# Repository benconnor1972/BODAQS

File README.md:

<table>
  <tr>
    <td width="50%">
      
    </td>

   <td width="50%">
      
    </td>
  </tr>
  <tr>
    <td width="50%">
      
    </td>
    <td width="50%">
      
    </td>
  </tr>
</table>

Current releases [here](https://github.com/benconnor1972/BODAQS/blob/main/RELEASES.md)

# Bicycle Open Data Acquisition System

BODAQS (Bicycle open data acquisition system) is an open-source, build-it-yourself data collection
and analysis system for mountain bikes, designed to be accessible to anyone with some DIY skills and a curiosity about what their bike is actually doing.

Data acquisition is ubiquitous in motorsport, and it's making its way into mountain-bike racing too. But for the engineering-minded (or budget-constrained), the choice is often between costly professional systems or consumer tools that keep the underlying data hidden.

BODAQS aims to offer an alternative: hardware that can be built with basic soldering skills using widely available parts; software with deep functionality and a structure designed for long-term expansion; and analysis built on powerful, free tools — alongside mounting and mechanical designs that can be 3D printed at home or produced at low cost. 

The project provides **open designs** for the hardware, software, analysis tools, and mechanical parts needed to collect and analyze mountain-bike data. It follows a build-it-yourself ethos, emphasising simplicity and low cost **without compromising functionality**.

## The problem with mountain bike (suspension) tuning

For most riders, suspension setup is a vibe-based, iterative guessing game: adjust a click, do a
run, wonder if that made things better or just 'different', repeat to exhaustion.

At the sharp end of gravity racing, teams with the budget chase these problems using data - but at a high cost. A few consumer products - notably Shockwiz, now owned by SRAM - have bridged the gap with a product that can provide meaningful suspension insight for most riders and be set up in under twenty minutes. But ShockWiz is a closed system: the algorithm is proprietary, the data never leaves the device, and if you run a coil shock, you're out of luck.

For the rider who wants to go deeper, wants to do more with the data, or whose coil setup isn't
supported,the choice has been: trust a black box, go all in on professional equipment, or go
without.

## The device

The BODAQS logger is a compact, hackable, open-source data logger you build yourself from widely available
components using basic soldering skills and a 3D printer. It records inputs from suspension and other sensors, at up to 1000Hz, and stores the data as standard CSV files readable by almost anything. The device can connect to wifi to allow settings to be edited or log files downloaded using any device with a web browser.

A small OLED screen and keypad make it simple to use, and an optional
handlebar-mounted button lets you tag moments of interest mid-ride — a heavy landing, a sketchy
section — so they're easy to find later.

The full design is open: PCB schematics and layouts, firmware, case, sensor mounts and more are all available to build, hack, and improve. There's a full bill of materials, build guide and advice on where to purchase the parts required.

## The software

Recording data is an engineering problem. Deciding what it means is the harder part, and the part that actually matters for tuning.

The BODAQS software comprises two main components:

- the **Import Manager** imports data from one or more loggers via file copy or WiFi, applies bike geometry information, does pre-processing calculations, matches GPS data from external devices and manages setup notes. The processed files live in your personal run library.
- the **BODAQS Workbench** gives you the visualization tools to dig deep into what your bike is doing.
The whole package can be installed on your computer and run with or without an internet connection.

## Who it's for

BODAQS is designed to scale with the user — in both the build, and the analysis.

If you're new to data acquisition, the hardware guide walks you through assembling the
logger, and you'll have something real to look at after your first ride with a couple of sensors - or even just one. 

If you're a top-end rider, mechanic or suspension shop with your own battle-tested ideas on how a bike should be set up, you'll have something you can use to test out and validate your own ideas and work, race faster, or to add value to your customers. 

If you're a tinkerer, engineer, developer, data scientist or uncategorised nerd, you can contribute to the project. Code, designs, ideas, feedback - it's all welcome.

## Enough of the pitch - where's this thing actually at?

**TL;DR:** we've got a pretty usable first-generation system that runs from end to end: From sourcing and building your logger to analyzing your runs. There's still lots to do, but we think it can add value for most people in its current state.

- The hardware works well within the limits of what we have tested and we think the user experience is pretty good. 
- The system supports analog potentiometers for suspension displacement, AS5600 (12-bit) and AS5048B (14-bit) rotary encoders for measuring linkage rotation, and GPS (either dedicated receiver or integrating data from Garmin devices).
- We have our own end-to-end software solution that you can download and test out, as well as a [hosted demo](https://demo.bodaqs.net/). We're also compatible with [data.syn.bike](https://data.syn.bike) if you prefer to see your data presented that away.
- We have [sourcing](https://bodaqs.net/logger-build-guide/bodaqs-a8/sourcing-hardware/), [building](https://bodaqs.net/logger-build-guide/bodaqs-a8/building-the-logger/), and [user](https://bodaqs.net/user-guide/) guides.
- We have published packages for the [hardware](https://github.com/benconnor1972/BODAQS/tree/main/hardware/releases) and the [3d printed parts](https://github.com/benconnor1972/BODAQS/tree/main/mechanical/Case/a8_v1_0)
- We have a set of Jupyter Lab [analysis notebooks](https://github.com/benconnor1972/BODAQS/releases) for exploratory data analysis. The back end code is organised in Python modules and there is a documented [API](https://github.com/benconnor1972/BODAQS/blob/main/docs/analysis/contracts/BODAQS_Public_API_Contract_v0.md). 

What we're working on:
- Further development of the software. There is lots we want to do!
- Extending the range of supported sensors. We've gone heavy (overkill?) on our software design to make integration of additional sensor types simple, so now is the time to cash in. Our next priorities are wheel speed sensors and inertia-motion units.
- Collecting build feedback from our beta testers. We're looking for people who want to help with this!
- Getting the system under some faster riders - in the end, we want to do *data analysis*, not just build hardware and software.

## Ethos and inspiration

This project exists for many reasons but three specific precursors stand out:
 - ShockWiz: Nigel Wade's ground-breaking product, now owned by SRAM, is in a category of one: mountain bike suspension analysis products that can be set up by an average user in under 20 minutes and provide useful feedback to the vast majority of riders. I was a happy ShockWiz user for many years and probably still would be if I hadn't discovered coil suspension. An elegant product that extracts maximum insight from minimum hardware, with a simplicity that hides some very clever engineering.
 - Sufni: The first open-source mountain bike data acquisition project to cross my path. For a variety of reasons I decided to take a different path rather than build one, but it provided the seed of the idea and the use of Lego for sensor mounting deserves a credit of its own.
 - RepRap: The movement that gave birth to cheap and ubiquitous 3D printing wasn't driven by market analysis by some big corporation, but by people who wanted a thing they couldn't buy (at a reasonable price). The community development and sharing ethos persists to this day and the products available are massively better and cheaper than what was available just a few years ago.

## Project maintenance

BODAQS is maintained by [Ben Connor](https://github.com/benconnor1972).

Contact: benconnor1972@gmail.com

Official release and code-signing responsibilities are described in the
[Code Signing Policy](CODE_SIGNING_POLICY.md).

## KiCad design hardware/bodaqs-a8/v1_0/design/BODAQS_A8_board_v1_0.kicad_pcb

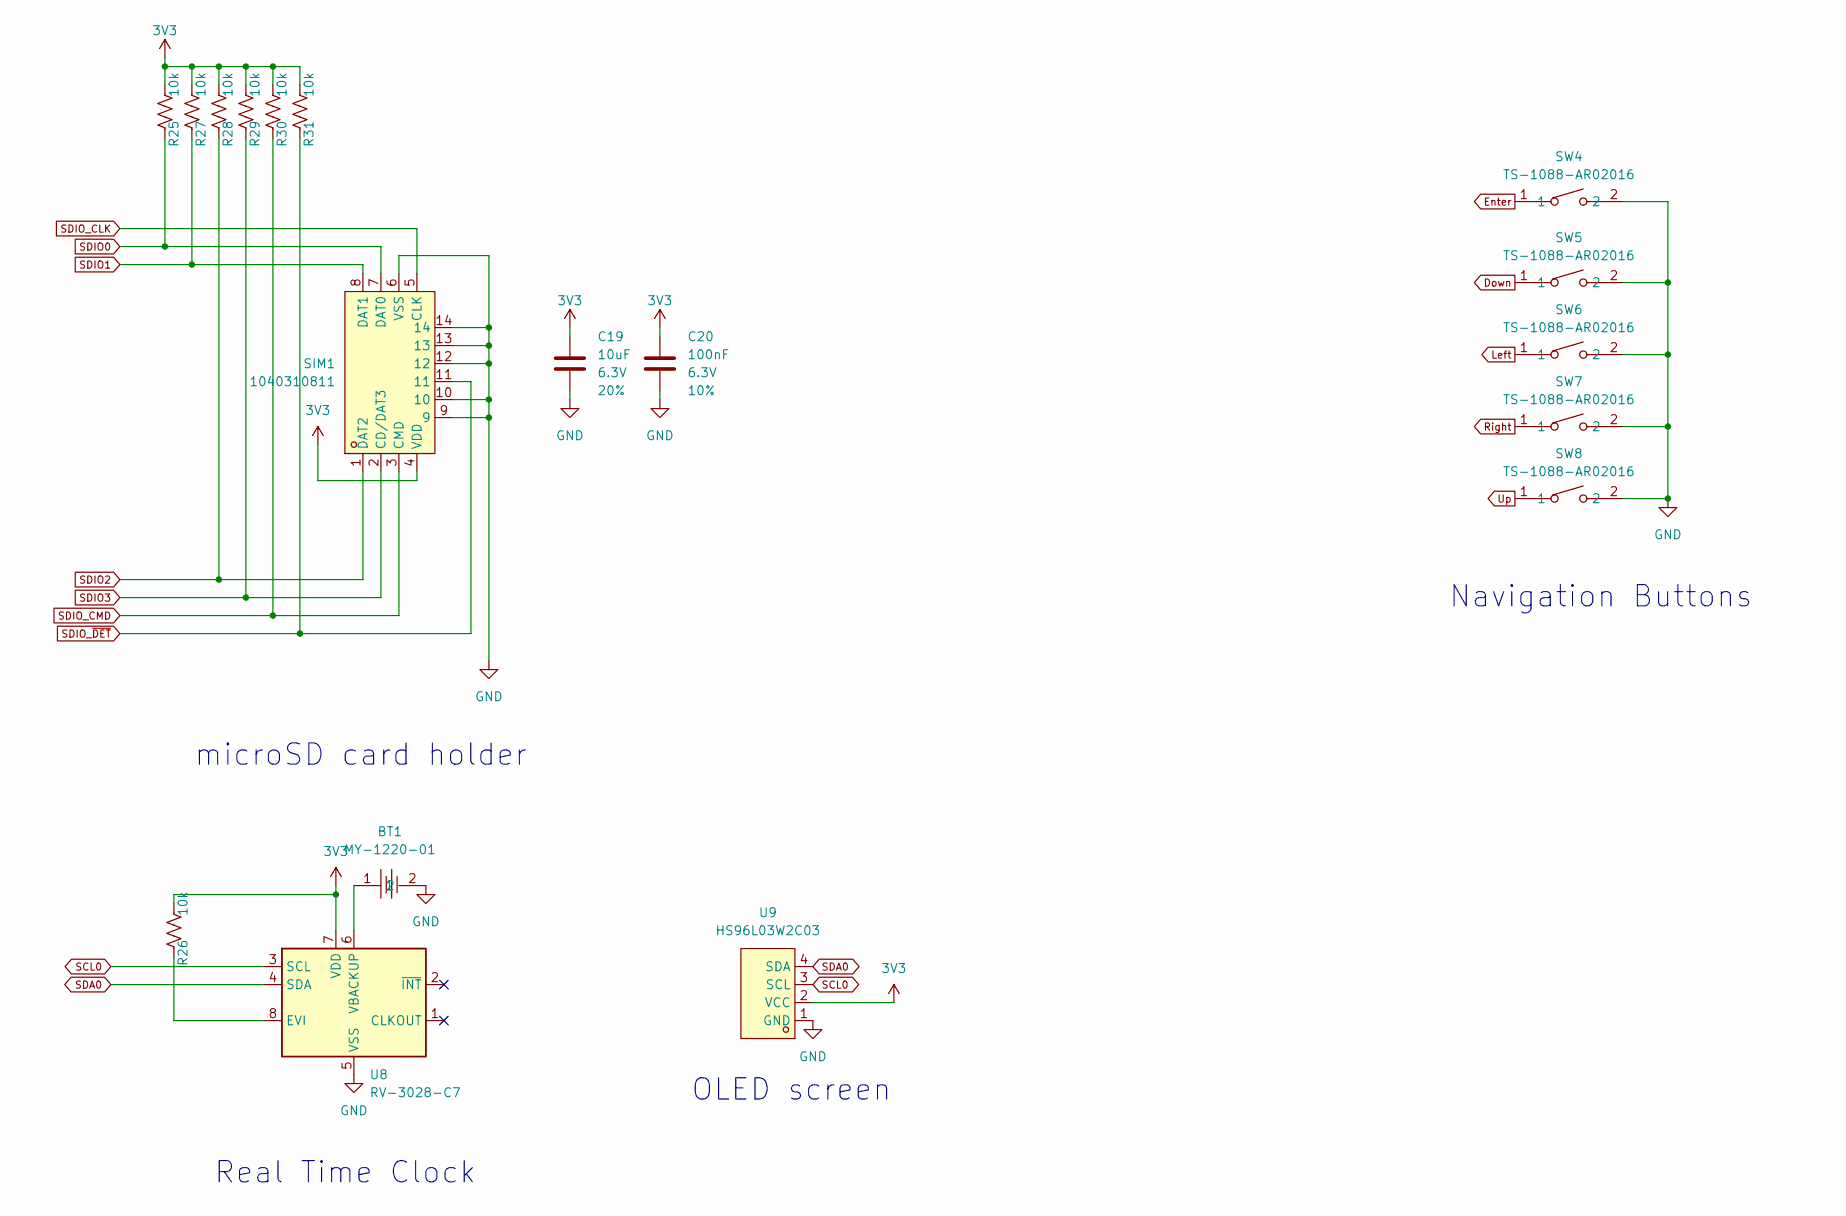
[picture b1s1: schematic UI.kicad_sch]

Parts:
BT1: MY-1220-01; BAT-TH_MY-1220-01; MPN MY-1220-01; LCSC Part C964817
C19: 10uF; C_0805_2012Metric; Voltage 6.3V; Tolerance 20%; Manufacturer_Part_Number CL21A106KAYNNNE; LCSC Part C15850
C20: 100nF; C_0402_1005Metric; Voltage 6.3V; Tolerance 10%; Manufacturer_Part_Number CL05B104KO5NNNC; LCSC Part C1525
R25, R26, R27, R28, R29, R30, R31: 10k; R_0402_1005Metric; Manufacturer_Part_Number 0402WGF1002TCE; LCSC Part C25744
SIM1: 1040310811; SIM-SMD_8P-1040310811; MPN 1040310811; LCSC Part C585350
SW4, SW5, SW6, SW7, SW8: TS-1088-AR02016; SW-SMD_L3.9-W3.0-P4.45; MPN TS-1088-AR02016; LCSC Part C720477
U8: RV-3028-C7; MicroCrystal_C7_SON-8_1.5x3.2mm_P0.9mm; Manufacturer_Part_Number RV-3028-C7-32.768kHz-1ppm-TA-QC; LCSC Part C3019759
U9: HS96L03W2C03; OLED-TH_L27.8-W27.2-P2.54_C9900033791; MPN HS96L03W2C03; LCSC Part C5248080

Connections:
3V3: C19.1, C20.2, R25.1, R26.1, R27.1, R28.1, R29.1, R30.1, R31.1, SIM1.4 (VDD), U8.7 (VDD), U9.2 (VCC); also elsewhere on the board
Down: SW5.1; also elsewhere on the board
Enter: SW4.1; also elsewhere on the board
GND: BT1.2, C19.2, C20.1, SIM1.6 (VSS), SIM1.9, SIM1.10, SIM1.12, SIM1.13, SIM1.14, SW4.2, SW5.2, SW6.2, SW7.2, SW8.2, U8.5 (VSS), U9.1 (GND); also elsewhere on the board
Left: SW6.1; also elsewhere on the board
unnamed: R26.2, U8.8 (EVI)
unnamed: BT1.1, U8.6 (VBACKUP)
Right: SW7.1; also elsewhere on the board
SCL0: U8.3 (SCL), U9.3 (SCL); also elsewhere on the board
SDA0: U8.4 (SDA), U9.4 (SDA); also elsewhere on the board
SDIO0: R25.2, SIM1.7 (DAT0); also elsewhere on the board
SDIO1: R27.2, SIM1.8 (DAT1); also elsewhere on the board
SDIO2: R28.2, SIM1.1 (DAT2); also elsewhere on the board
SDIO3: R29.2, SIM1.2 (CD/DAT3); also elsewhere on the board
SDIO_CLK: SIM1.5 (CLK); also elsewhere on the board
SDIO_CMD: R30.2, SIM1.3 (CMD); also elsewhere on the board
SDIO_~DET: R31.2, SIM1.11; also elsewhere on the board
Up: SW8.1; also elsewhere on the board

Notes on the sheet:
OLED screen
Real Time Clock
Navigation Buttons
microSD card holder

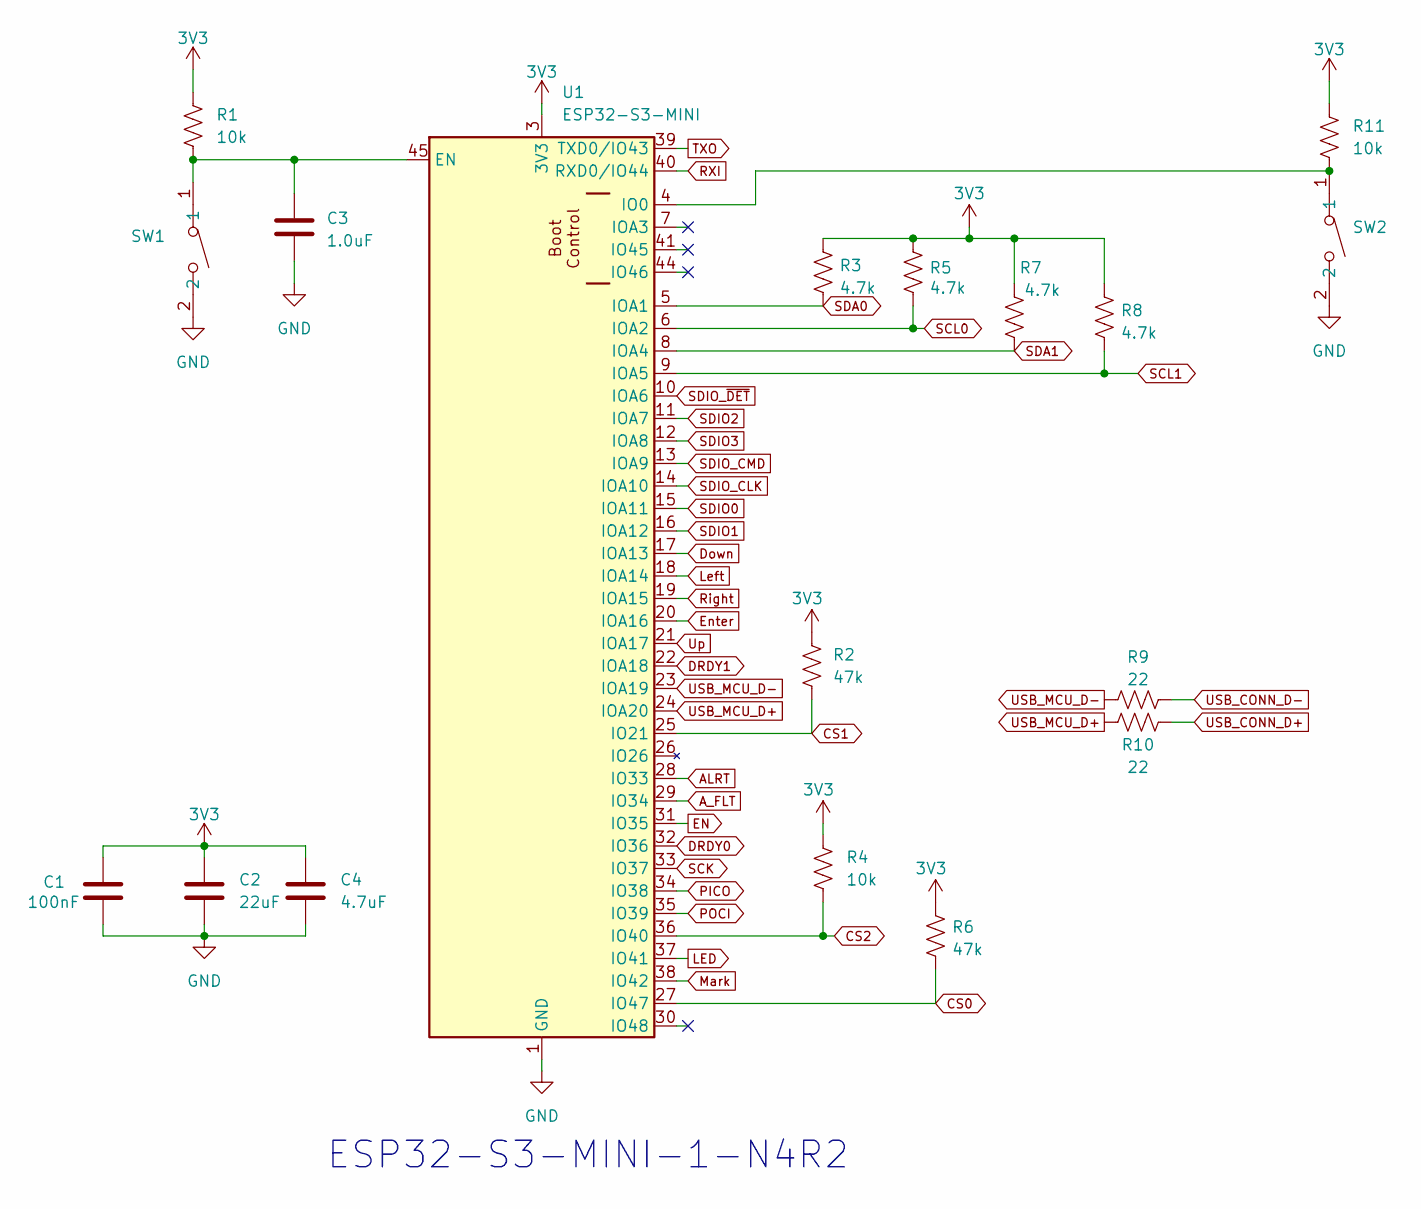
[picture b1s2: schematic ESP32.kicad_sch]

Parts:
C1: 100nF; C_0402_1005Metric; Manufacturer_Part_Number CL05B104KO5NNNC; LCSC Part C1525
C2: 22uF; C_0603_1608Metric; Voltage 6.3V; Tolerance 20%; Manufacturer_Part_Number GRM188R61A226ME15D; LCSC Part C84419
C3: 1.0uF; C_0402_1005Metric; Voltage 16V; Tolerance 10%; Manufacturer_Part_Number CL05A105KA5NQNC; LCSC Part C52923
C4: 4.7uF; C_0402_1005Metric; Voltage 6.3V; Tolerance 20%; Manufacturer_Part_Number CL05A475MP5NRNC; LCSC Part C23733
R1, R4, R11: 10k; R_0402_1005Metric; Manufacturer_Part_Number 0402WGF1002TCE; LCSC Part C25744
R2, R6: 47k; R_0402_1005Metric; Manufacturer_Part_Number 0402WGF4702TCE; LCSC Part C25792
R3, R5, R7, R8: 4.7k; R_0402_1005Metric; Manufacturer_Part_Number 0402WGF4701TCE; LCSC Part C25900
R9, R10: 22; R_0402_1005Metric; Manufacturer_Part_Number 0402WGF220JTCE; LCSC Part C25092
SW1, SW2: TS-1088-AR02016; SW-SMD_L3.9-W3.0-P4.45; MPN TS-1088-AR02016; LCSC Part C720477
U1: ESP32-S3-MINI; ESP32-S2-MINI-1; Manufacturer_Part_Number ESP32-S3-MINI-1-N4R2; LCSC Part C3013941

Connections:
3V3: C1.1, C2.2, C4.1, R1.1, R2.1, R3.2, R4.1, R5.2, R6.1, R7.2, R8.2, R11.1, U1.3 (3V3); also elsewhere on the board
LED: U1.37 (IO41); also elsewhere on the board
POCI: U1.35 (IO39); also elsewhere on the board
TXO: U1.39 (TXD0/IO43); also elsewhere on the board
ALRT: U1.28 (IO33); also elsewhere on the board
A_FLT: U1.29 (IO34); also elsewhere on the board
CS0: R6.2, U1.27 (IO47); also elsewhere on the board
CS1: R2.2, U1.25 (IO21); also elsewhere on the board
CS2: R4.2, U1.36 (IO40); also elsewhere on the board
DRDY0: U1.32 (IO36); also elsewhere on the board
DRDY1: U1.22 (IOA18); also elsewhere on the board
Down: U1.17 (IOA13); also elsewhere on the board
EN: U1.31 (IO35); also elsewhere on the board
Enter: U1.20 (IOA16); also elsewhere on the board
GND: C1.2, C2.1, C3.2, C4.2, SW1.2, SW2.2, U1.1 (GND), U1.2 (GND), U1.42 (GND), U1.43 (GND), U1.46 (GND), U1.47 (GND), U1.48 (GND), U1.49 (GND), U1.50 (GND), U1.51 (GND), U1.52 (GND), U1.53 (GND), U1.54 (GND), U1.55 (GND), U1.56 (GND), U1.57 (GND), U1.58 (GND), U1.59 (GND), U1.60 (GND), U1.61 (GND), U1.62 (GND), U1.63 (GND), U1.64 (GND), U1.65 (GND); also elsewhere on the board
Left: U1.18 (IOA14); also elsewhere on the board
Mark: U1.38 (IO42); also elsewhere on the board
unnamed: C3.1, R1.2, SW1.1, U1.45 (EN)
unnamed: R11.2, SW2.1, U1.4 (IO0)
PICO: U1.34 (IO38); also elsewhere on the board
RXI: U1.40 (RXD0/IO44); also elsewhere on the board
Right: U1.19 (IOA15); also elsewhere on the board
SCK: U1.33 (IO37); also elsewhere on the board
SCL0: R5.1, U1.6 (IOA2); also elsewhere on the board
SCL1: R8.1, U1.9 (IOA5); also elsewhere on the board
SDA0: R3.1, U1.5 (IOA1); also elsewhere on the board
SDA1: R7.1, U1.8 (IOA4); also elsewhere on the board
SDIO0: U1.15 (IOA11); also elsewhere on the board
SDIO1: U1.16 (IOA12); also elsewhere on the board
SDIO2: U1.11 (IOA7); also elsewhere on the board
SDIO3: U1.12 (IOA8); also elsewhere on the board
SDIO_CLK: U1.14 (IOA10); also elsewhere on the board
SDIO_CMD: U1.13 (IOA9); also elsewhere on the board
SDIO_~DET: U1.10 (IOA6); also elsewhere on the board
USB_CONN_D+: R10.2; also elsewhere on the board
USB_CONN_D-: R9.2; also elsewhere on the board
USB_MCU_D+: R10.1, U1.24 (IOA20)
USB_MCU_D-: R9.1, U1.23 (IOA19)
Up: U1.21 (IOA17); also elsewhere on the board

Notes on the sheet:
ESP32-S3-MINI-1-N4R2

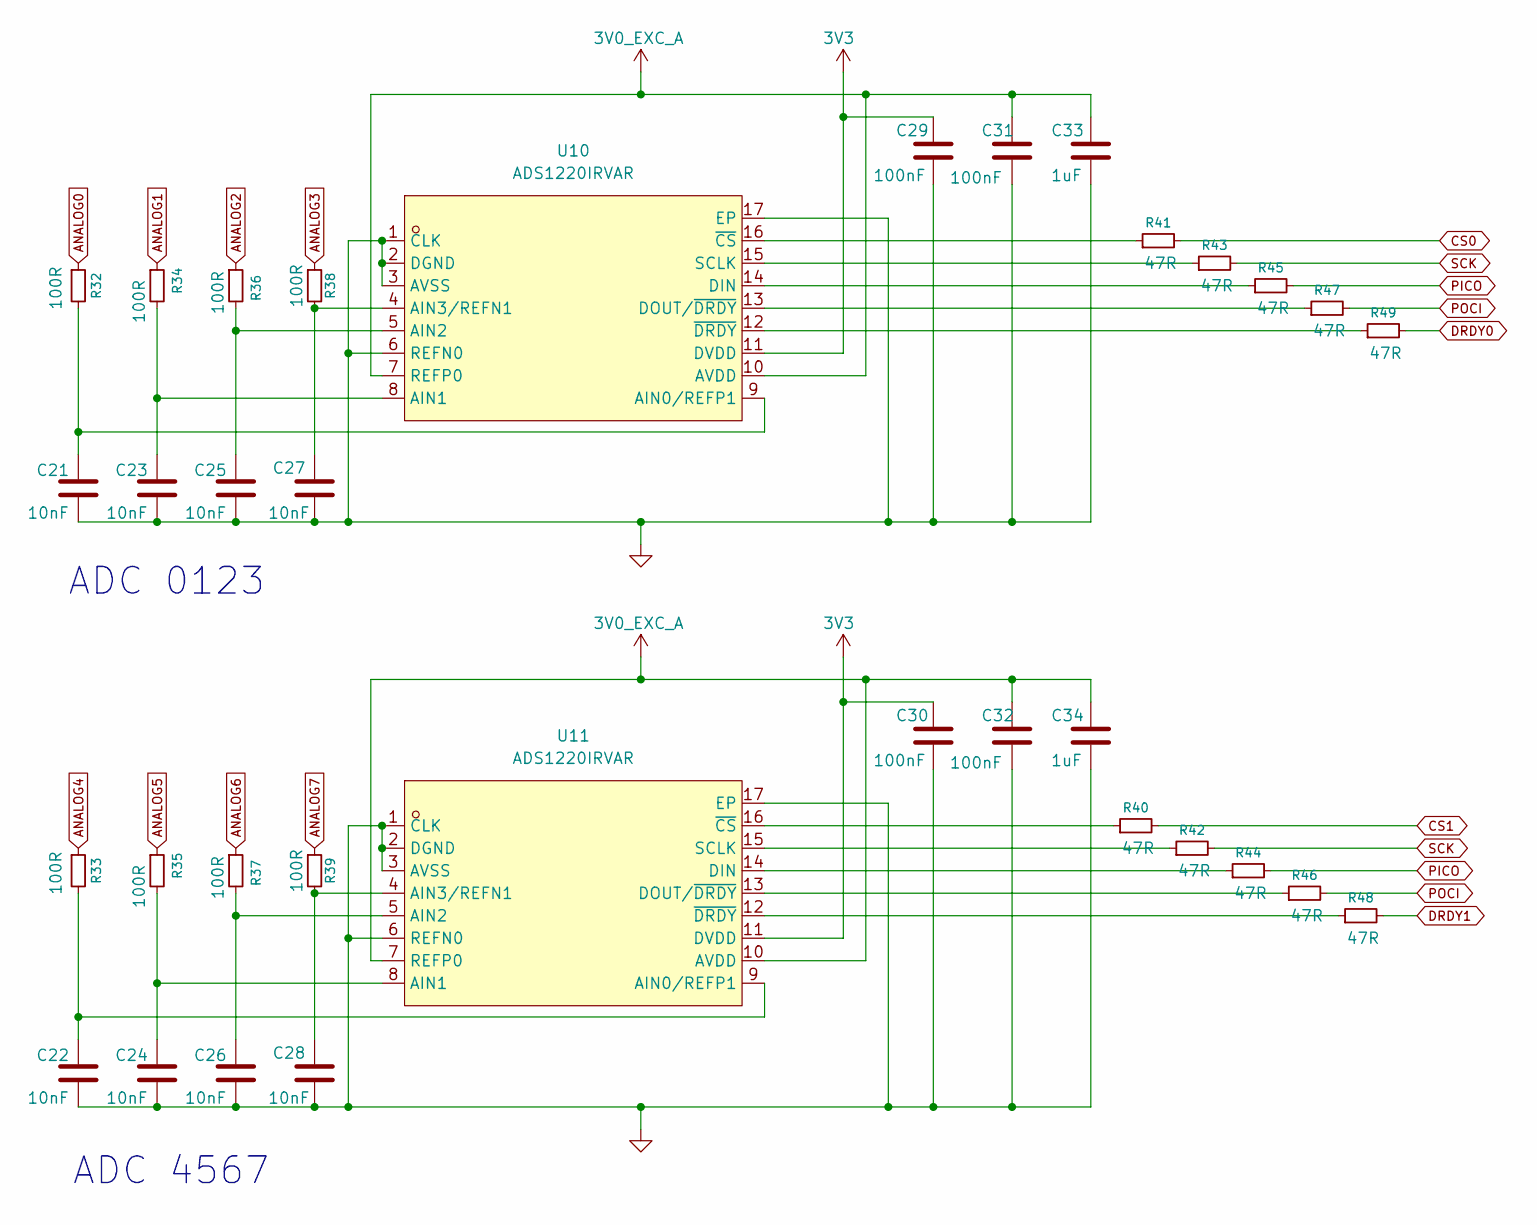
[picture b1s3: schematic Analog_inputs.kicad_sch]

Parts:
C21, C22, C23, C24, C25, C26, C27, C28: 10nF; C_0402_1005Metric; Manufacturer_Part_Number CL05B103KB5NNNC; LCSC Part C15195
C29, C30, C31, C32: 100nF; C_0402_1005Metric; Manufacturer_Part_Number CL05B104KO5NNNC; LCSC Part C1525
C33, C34: 1uF; C_0402_1005Metric; Manufacturer_Part_Number CL05A105KA5NQNC; LCSC Part C52923
R32, R33, R34, R35, R36, R37, R38, R39: 100R; R_0402_1005Metric; Manufacturer_Part_Number 0402WGF1000TCE; LCSC Part C25076
R40, R41, R42, R43, R44, R45, R46, R47, R48, R49: 47R; R_0402_1005Metric; Manufacturer_Part_Number 0402WGF499JTCE; LCSC Part C25120
U10, U11: ADS1220IRVAR; VQFN-16_L3.5-W3.5-P0.50-BL-EP2.1; MPN ADS1220IRVAR; LCSC Part C2651338

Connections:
3V0_EXC_A: C31.1, C32.1, C33.1, C34.1, U10.7 (REFP0), U10.10 (AVDD), U11.7 (REFP0), U11.10 (AVDD); also elsewhere on the board
3V3: C29.1, C30.1, U10.11 (DVDD), U11.11 (DVDD); also elsewhere on the board
POCI: R46.2, R47.2; also elsewhere on the board
ANALOG0: R32.1; also elsewhere on the board
ANALOG1: R34.1; also elsewhere on the board
ANALOG2: R36.1; also elsewhere on the board
ANALOG3: R38.1; also elsewhere on the board
ANALOG4: R33.1; also elsewhere on the board
ANALOG5: R35.1; also elsewhere on the board
ANALOG6: R37.1; also elsewhere on the board
ANALOG7: R39.1; also elsewhere on the board
CS0: R41.2; also elsewhere on the board
CS1: R40.2; also elsewhere on the board
DRDY0: R49.2; also elsewhere on the board
DRDY1: R48.2; also elsewhere on the board
GND: C21.2, C22.2, C23.2, C24.2, C25.2, C26.2, C27.2, C28.2, C29.2, C30.2, C31.2, C32.2, C33.2, C34.2, U10.1 (CLK), U10.2 (DGND), U10.3 (AVSS), U10.6 (REFN0), U10.17 (EP), U11.1 (CLK), U11.2 (DGND), U11.3 (AVSS), U11.6 (REFN0), U11.17 (EP); also elsewhere on the board
unnamed: C21.1, R32.2, U10.9 (AIN0/REFP1)
unnamed: C23.1, R34.2, U10.8 (AIN1)
unnamed: C25.1, R36.2, U10.5 (AIN2)
unnamed: C27.1, R38.2, U10.4 (AIN3/REFN1)
unnamed: R45.1, U10.14 (DIN)
unnamed: R47.1, U10.13 (DOUT/~DRDY)
unnamed: R43.1, U10.15 (SCLK)
unnamed: R41.1, U10.16 (~CS)
unnamed: R49.1, U10.12 (~DRDY)
unnamed: C22.1, R33.2, U11.9 (AIN0/REFP1)
unnamed: C24.1, R35.2, U11.8 (AIN1)
unnamed: C26.1, R37.2, U11.5 (AIN2)
unnamed: C28.1, R39.2, U11.4 (AIN3/REFN1)
unnamed: R44.1, U11.14 (DIN)
unnamed: R46.1, U11.13 (DOUT/~DRDY)
unnamed: R42.1, U11.15 (SCLK)
unnamed: R40.1, U11.16 (~CS)
unnamed: R48.1, U11.12 (~DRDY)
PICO: R44.2, R45.2; also elsewhere on the board
SCK: R42.2, R43.2; also elsewhere on the board

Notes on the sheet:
ADC 4567
ADC 0123

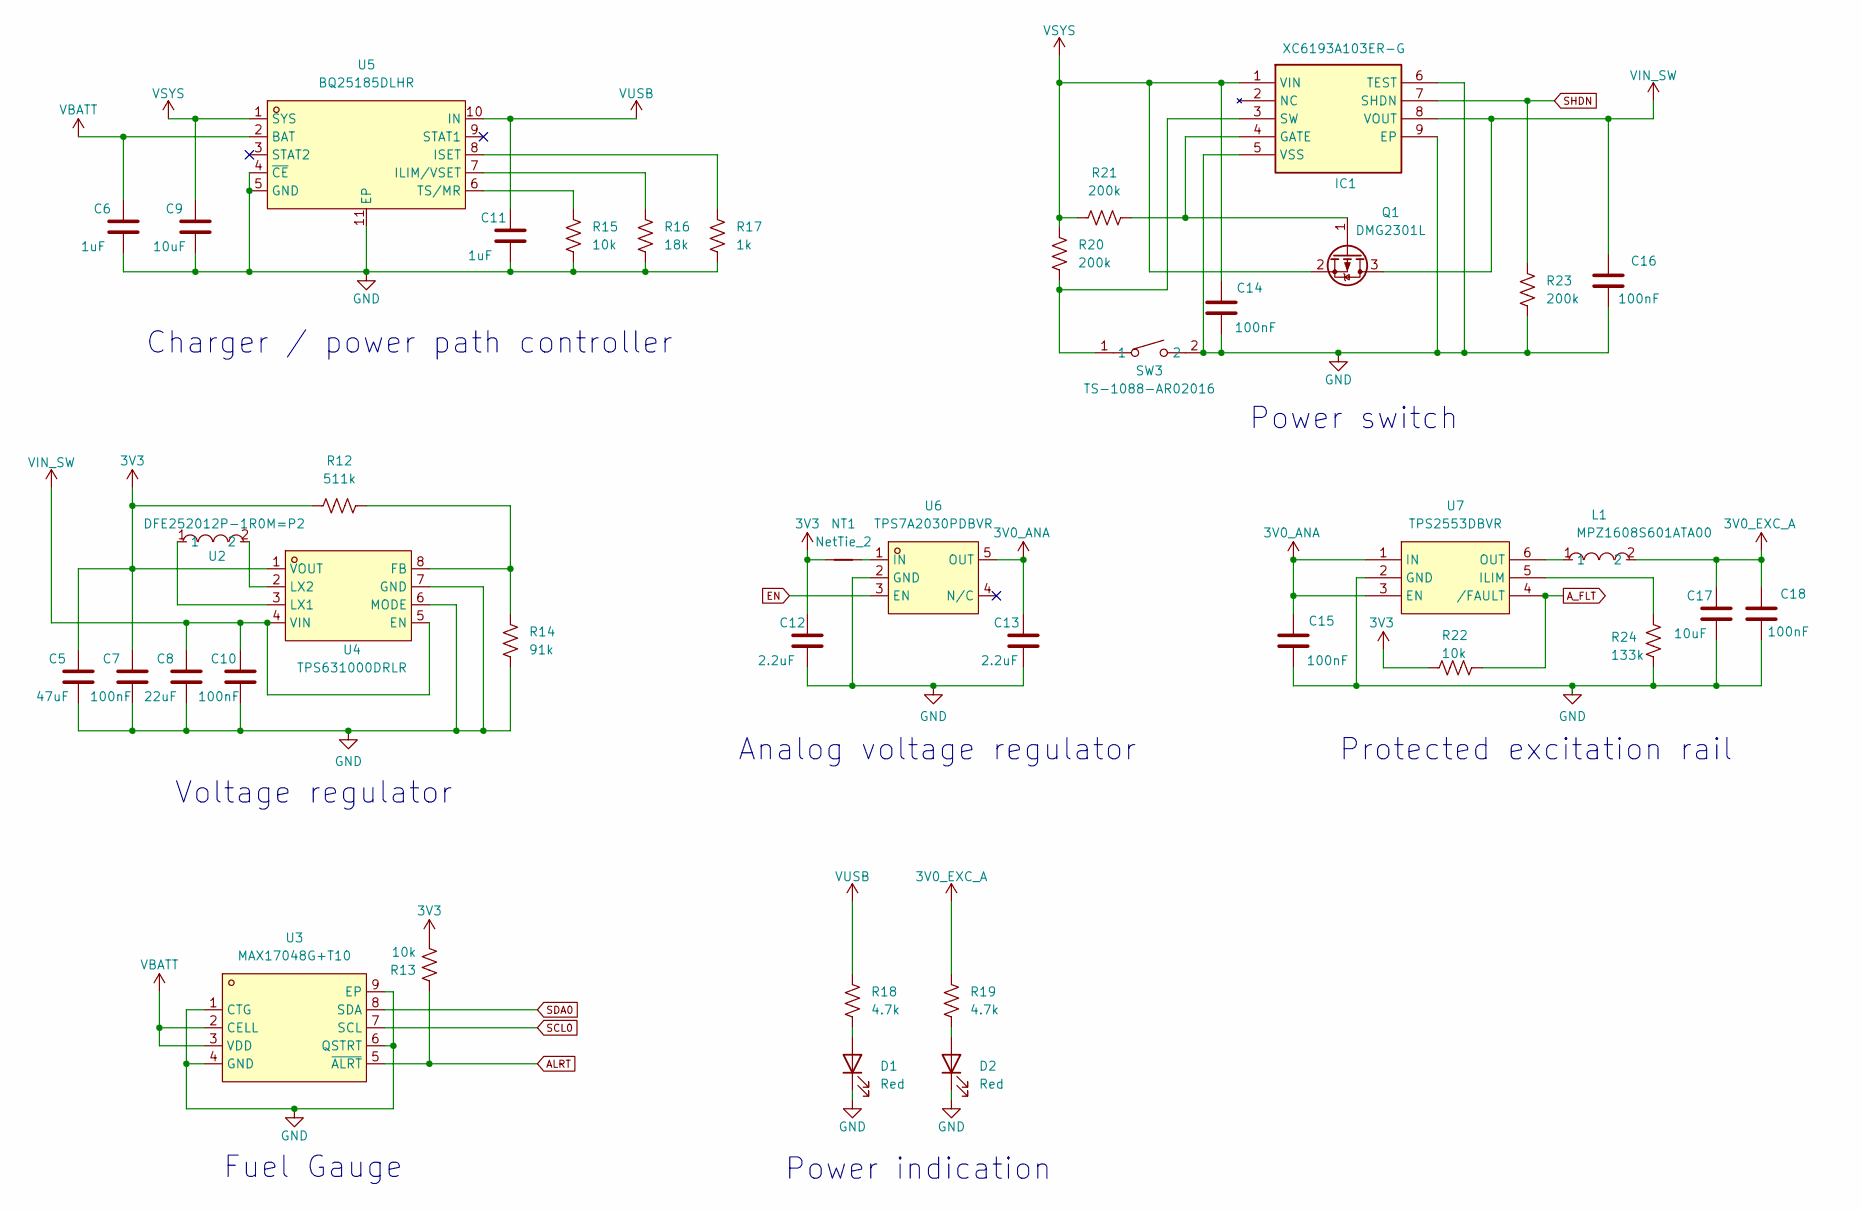
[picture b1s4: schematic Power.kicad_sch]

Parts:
C5: 47uF; C_0805_2012Metric; Manufacturer_Part_Number CL21A476MQYNNNE; LCSC Part C16780
C6, C11: 1uF; C_0402_1005Metric; Manufacturer_Part_Number CL05A105KA5NQNC; LCSC Part C52923
C7, C10, C14, C15, C16, C18: 100nF; C_0402_1005Metric; Manufacturer_Part_Number CL05B104KO5NNNC; LCSC Part C1525
C8: 22uF; C_0603_1608Metric; Manufacturer_Part_Number GRM188R61A226ME15D; LCSC Part C84419
C9, C17: 10uF; C_0805_2012Metric; Manufacturer_Part_Number CL21A106KAYNNNE; LCSC Part C15850
C12, C13: 2.2uF; C_0603_1608Metric; Manufacturer_Part_Number CL10A225KO8NNNC; LCSC Part C23630
D1, D2: Red; LED_0603_1608Metric; Manufacturer_Part_Number Hubei KENTO KT-0603R; LCSC Part C2286
IC1: XC6193A103ER-G; XC6193AA05ERG; Manufacturer_Part_Number XC6193A103ER-G; LCSC Part C19267155
L1: MPZ1608S601ATA00; L0603; MPN MPZ1608S601ATA00; LCSC Part C107335
NT1: NetTie_2; NetTie-2_SMD_Pad0.5mm
Q1: DMG2301L; SOT-23; Manufacturer_Part_Number DMG2301L-7; LCSC Part C102619
R12: 511k; R_0402_1005Metric; Manufacturer_Part_Number 0402WGF5113TCE; LCSC Part C64042
R13, R15, R22: 10k; R_0402_1005Metric; Manufacturer_Part_Number 0402WGF1002TCE; LCSC Part C25744
R14: 91k; R_0402_1005Metric; Manufacturer_Part_Number 0402WGF9102TCE; LCSC Part C4147
R16: 18k; R_0402_1005Metric; Manufacturer_Part_Number 0402WGF1802TCE; LCSC Part C25762
R17: 1k; R_0402_1005Metric; Manufacturer_Part_Number 0402WGF1001TCE; LCSC Part C11702
R18, R19: 4.7k; R_0402_1005Metric; Manufacturer_Part_Number 0402WGF4701TCE; LCSC Part C25900
R20, R21, R23: 200k; R_0402_1005Metric; Manufacturer_Part_Number 0402WGF2003TCE; LCSC Part C25764
R24: 133k; R_0402_1005Metric; Manufacturer_Part_Number 0402WGF1333TCE; LCSC Part C25753
SW3: TS-1088-AR02016; SW-SMD_L3.9-W3.0-P4.45; MPN TS-1088-AR02016; LCSC Part C720477
U2: DFE252012P-1R0M=P2; L1008; MPN DFE252012P-1R0M=P2; LCSC Part C882955
U3: MAX17048G+T10; TDFN-8_L2.0-W2.0-P0.50-BL-EP1.2; MPN MAX17048G+T10; LCSC Part C2682616
U4: TPS631000DRLR; SOT-583-8_L2.1-W1.2-P0.50-LS1.6-BL; MPN TPS631000DRLR; LCSC Part C5219190
U5: BQ25185DLHR; WSON-10_L2.2-W2.0-P0.40-BL-EP_TI_DLH0010A; MPN BQ25185DLHR; LCSC Part C19725033
U6: TPS7A2030PDBVR; TSOT-23-5_L2.9-W1.6-P0.95-LS2.8-BR; MPN TPS7A2030PDBVR; LCSC Part C963429
U7: TPS2553DBVR; SOT-23-6_L2.9-W1.6-P0.95-LS2.8-BR; MPN TPS2553DBVR; LCSC Part C55266

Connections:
3V0_ANA: C13.1, C15.1, U6.5 (OUT), U7.1 (IN), U7.3 (EN)
3V0_EXC_A: C17.1, C18.1, L1.2, R19.1; also elsewhere on the board
3V3: C5.1, C7.1, C12.1, NT1.1, R12.1, R13.1, R22.2, U4.1 (VOUT); also elsewhere on the board
ALRT: R13.2, U3.5 (~ALRT); also elsewhere on the board
A_FLT: R22.1, U7.4 (/FAULT); also elsewhere on the board
EN: U6.3 (EN); also elsewhere on the board
GND: C5.2, C6.2, C7.2, C8.2, C9.2, C10.2, C11.2, C12.2, C13.2, C14.2, C15.2, C16.2, C17.2, C18.2, D1.1 (K), D2.1 (K), IC1.5 (VSS), IC1.6 (TEST), IC1.9 (EP), R14.2, R15.2, R16.2, R17.2, R23.2, R24.1, SW3.2, U3.1 (CTG), U3.4 (GND), U3.6 (QSTRT), U3.9 (EP), U4.6 (MODE), U4.7 (GND), U5.4 (~CE), U5.5 (GND), U5.11 (EP), U6.2 (GND), U7.2 (GND); also elsewhere on the board
unnamed: D1.2 (A), R18.2
unnamed: D2.2 (A), R19.2
unnamed: IC1.4 (GATE), Q1.1 (G), R21.2
unnamed: IC1.3 (SW), R20.2, SW3.1
unnamed: R12.2, R14.1, U4.8 (FB)
unnamed: U2.1, U4.3 (LX1)
unnamed: U2.2, U4.2 (LX2)
unnamed: R16.1, U5.7 (ILIM/VSET)
unnamed: R17.1, U5.8 (ISET)
unnamed: R15.1, U5.6 (TS/MR)
unnamed: NT1.2, U6.1 (IN)
unnamed: R24.2, U7.5 (ILIM)
unnamed: L1.1, U7.6 (OUT)
SCL0: U3.7 (SCL); also elsewhere on the board
SDA0: U3.8 (SDA); also elsewhere on the board
SHDN: IC1.7 (SHDN), R23.1
VBATT: C6.1, U3.2 (CELL), U3.3 (VDD), U5.2 (BAT); also elsewhere on the board
VIN_SW: C8.1, C10.1, C16.1, IC1.8 (VOUT), Q1.3 (D), U4.4 (VIN), U4.5 (EN)
VSYS: C9.1, C14.1, IC1.1 (VIN), Q1.2 (S), R20.1, R21.1, U5.1 (SYS)
VUSB: C11.1, R18.1, U5.10 (IN); also elsewhere on the board

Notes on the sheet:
Power indication
Charger / power path controller
Protected excitation rail
Voltage regulator
Fuel Gauge
Analog voltage regulator
Power switch

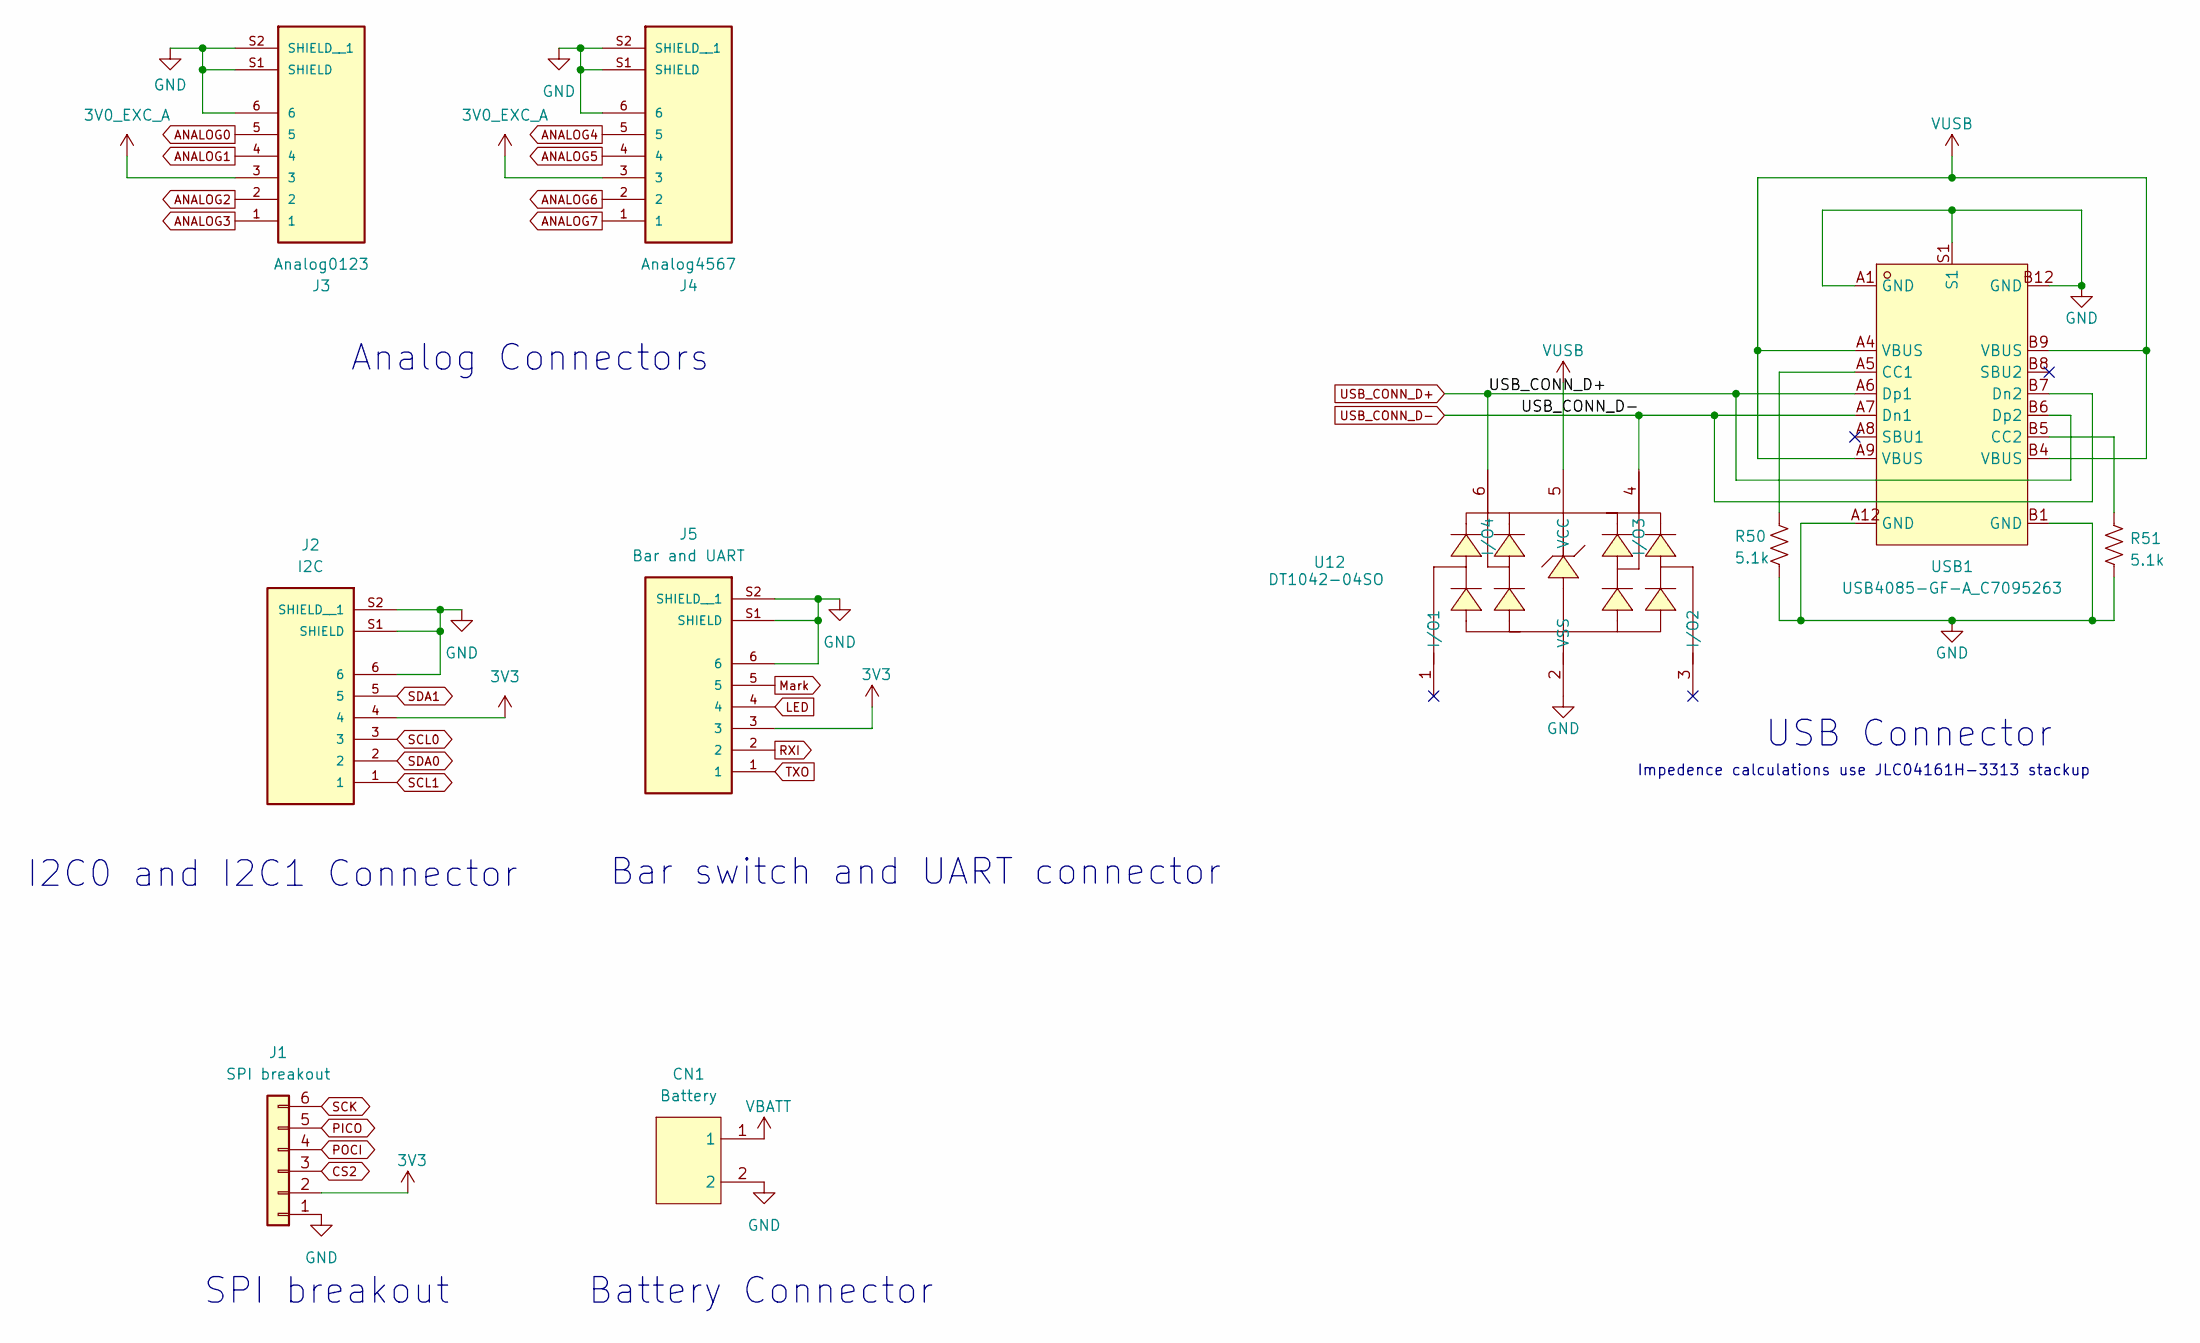
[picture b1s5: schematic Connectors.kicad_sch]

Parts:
CN1: Battery; CONN-TH_B2B-PH-K-S; MPN B2B-PH-K-S(LF)(SN); LCSC Part C131337
J1: SPI breakout; JST_XA_B06B-XASK-1_1x06_P2.50mm_Vertical
J2: I2C; AMPHENOL_M8AS-06PMMR-SF8001; PARTREV A
J3: Analog0123; AMPHENOL_M8AS-06PMMR-SF8001; PARTREV A
J4: Analog4567; AMPHENOL_M8AS-06PMMR-SF8001; PARTREV A
J5: Bar and UART; AMPHENOL_M8AS-06PMMR-SF8001; PARTREV A
R50, R51: 5.1k; R_0402_1005Metric; Manufacturer_Part_Number 0402WGF5101TCE; LCSC Part C25905
U12: DT1042-04SO; SOT-23-6_L2.9-W1.6-P0.95-LS2.8-BR; MPN DT1042-04SO-7(UMW); LCSC Part C19626385
USB1: USB4085-GF-A_C7095263; USC-C-SMD_USB4085-GF-A; MPN USB4085-GF-A; LCSC Part C7095263

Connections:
3V0_EXC_A: J3.3, J4.3; also elsewhere on the board
3V3: J1.2, J2.4, J5.3; also elsewhere on the board
LED: J5.4; also elsewhere on the board
POCI: J1.4; also elsewhere on the board
TXO: J5.1; also elsewhere on the board
ANALOG0: J3.5; also elsewhere on the board
ANALOG1: J3.4; also elsewhere on the board
ANALOG2: J3.2; also elsewhere on the board
ANALOG3: J3.1; also elsewhere on the board
ANALOG4: J4.5; also elsewhere on the board
ANALOG5: J4.4; also elsewhere on the board
ANALOG6: J4.2; also elsewhere on the board
ANALOG7: J4.1; also elsewhere on the board
CS2: J1.3; also elsewhere on the board
GND: CN1.2, J1.1, J2.6, J2.S1 (SHIELD), J2.S2 (SHIELD__1), J3.6, J3.S1 (SHIELD), J3.S2 (SHIELD__1), J4.6, J4.S1 (SHIELD), J4.S2 (SHIELD__1), J5.6, J5.S1 (SHIELD), J5.S2 (SHIELD__1), R50.2, R51.1, U12.2 (VSS), USB1.A1 (GND), USB1.A12 (GND), USB1.B1 (GND), USB1.B12 (GND), USB1.S1; also elsewhere on the board
Mark: J5.5; also elsewhere on the board
unnamed: R50.1, USB1.A5 (CC1)
unnamed: R51.2, USB1.B5 (CC2)
PICO: J1.5; also elsewhere on the board
RXI: J5.2; also elsewhere on the board
SCK: J1.6; also elsewhere on the board
SCL0: J2.3; also elsewhere on the board
SCL1: J2.1; also elsewhere on the board
SDA0: J2.2; also elsewhere on the board
SDA1: J2.5; also elsewhere on the board
USB_CONN_D+: U12.6 (I/O4), USB1.A6 (Dp1), USB1.B6 (Dp2); also elsewhere on the board
USB_CONN_D-: U12.4 (I/O3), USB1.A7 (Dn1), USB1.B7 (Dn2); also elsewhere on the board
VBATT: CN1.1; also elsewhere on the board
VUSB: U12.5 (VCC), USB1.A4 (VBUS), USB1.A9 (VBUS), USB1.B4 (VBUS), USB1.B9 (VBUS); also elsewhere on the board

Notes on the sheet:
I2C0 and I2C1 Connector
SPI breakout
Analog Connectors
Impedence calculations use JLC04161H-3313 stackup
USB Connector
Bar switch and UART connector
Battery Connector
